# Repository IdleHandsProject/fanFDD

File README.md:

# fanFDD
The firmware and CAD for the neural network fan fault detector.

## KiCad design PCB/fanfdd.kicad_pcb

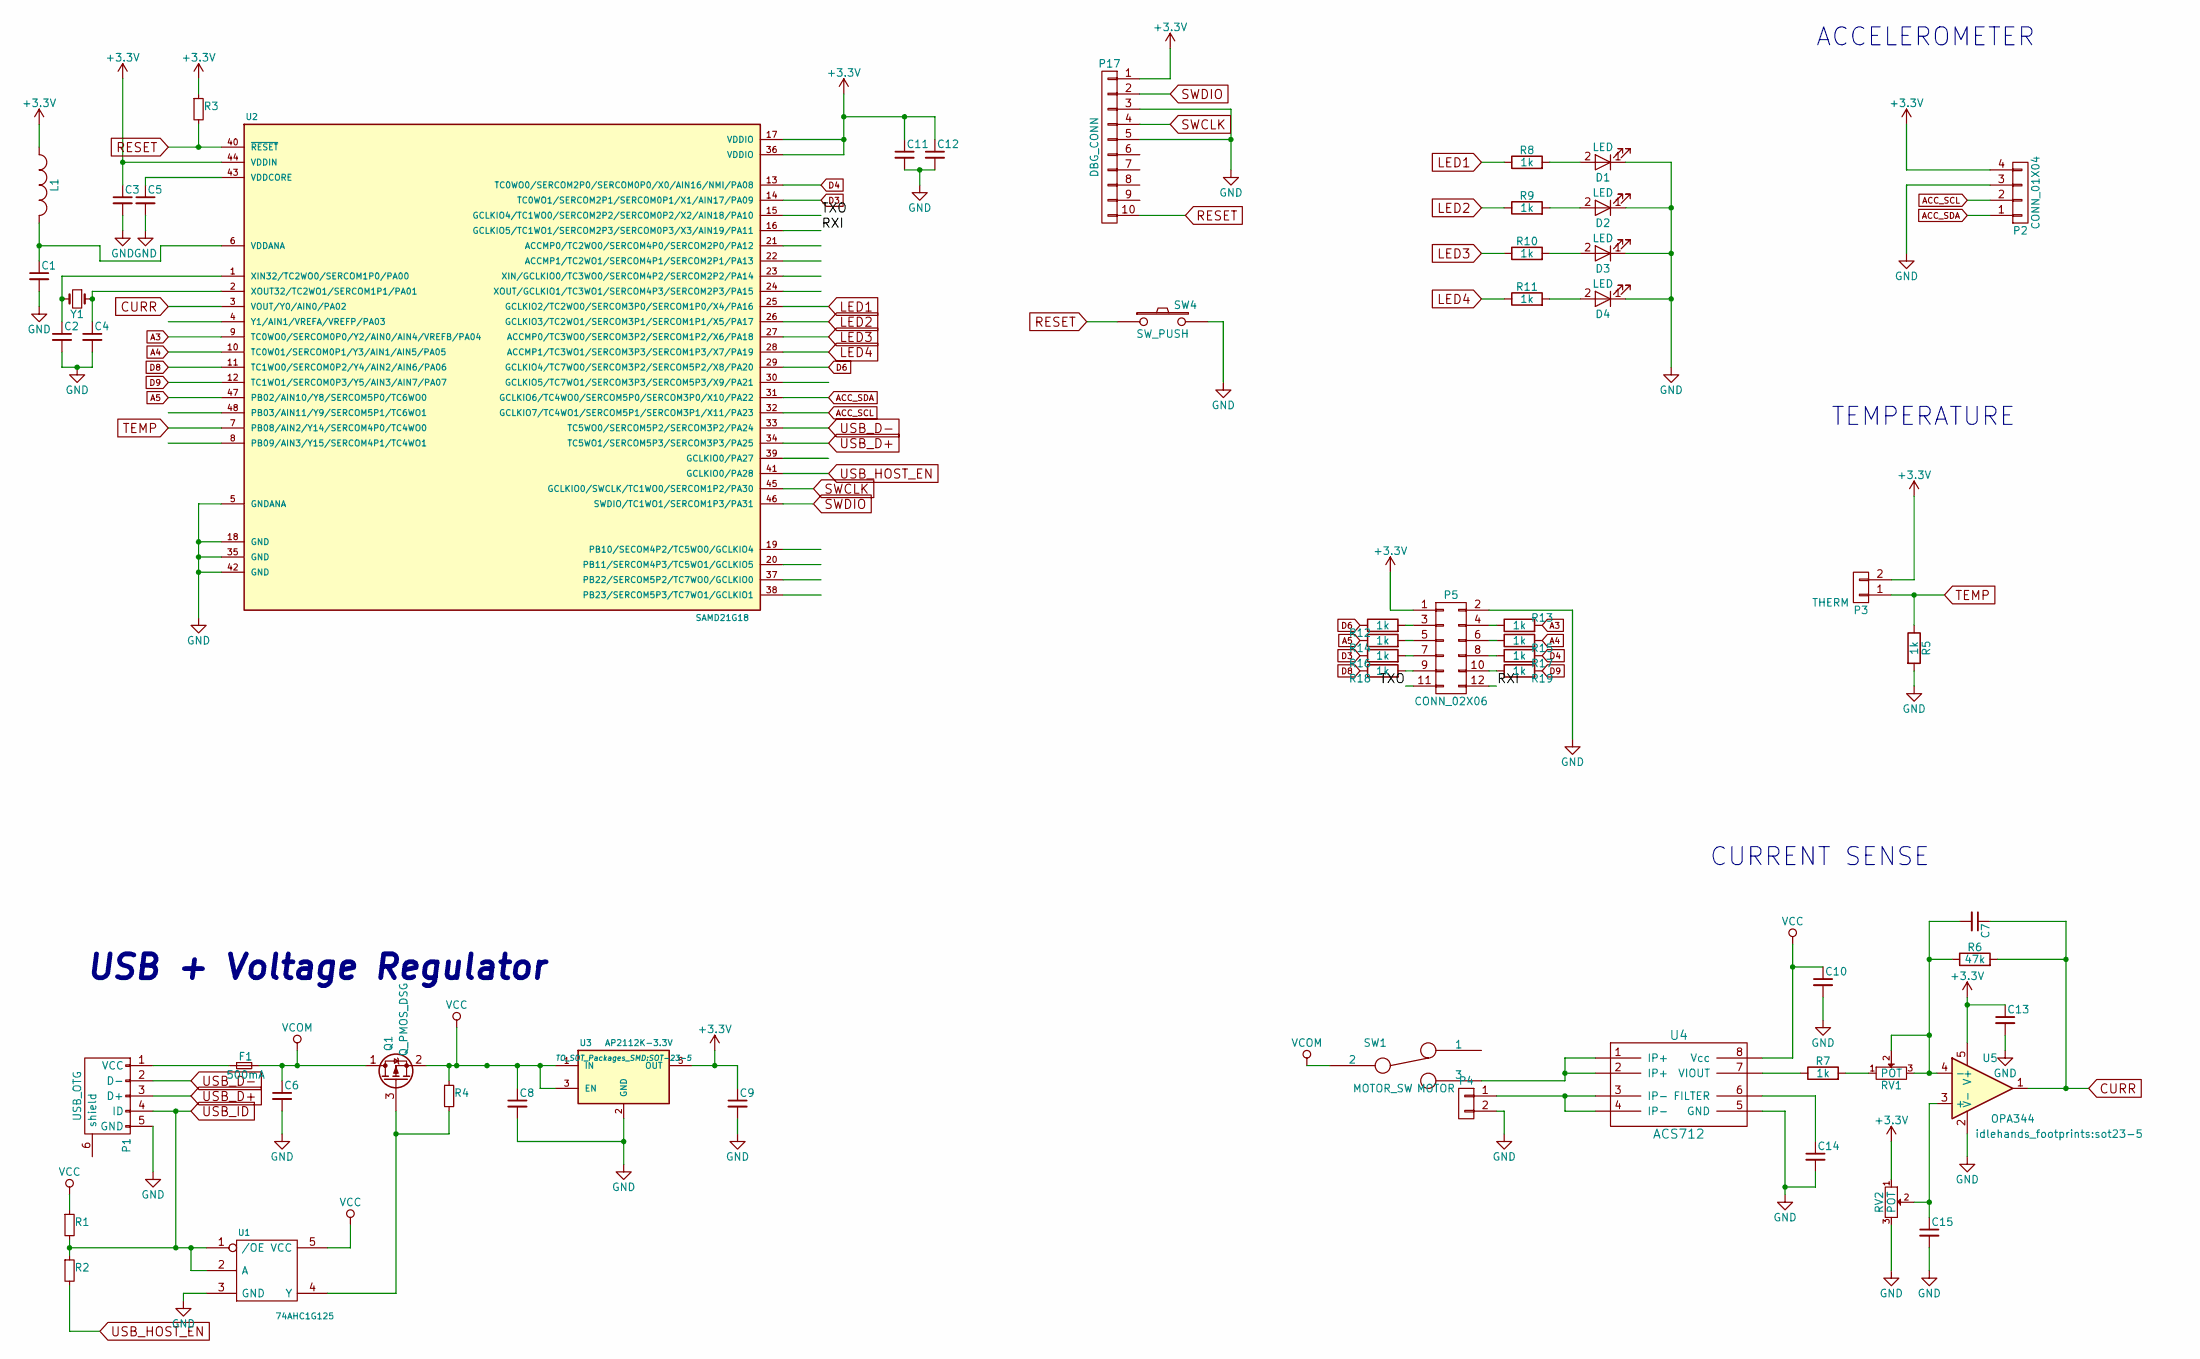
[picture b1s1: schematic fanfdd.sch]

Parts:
C1, C3, C5, C10, C11, C12, C13, C15: 0.1uF; C_0805; Digikey Part No. 1276-1286-1-ND
C2, C4: 15pF; C_0402_Hand; Digikey Part No. 712-1261-1-ND
C6, C9: 2.2uF; C_0805; Digikey Part No. 311-3446-1-ND
C7: 100pF; C_0805; Digikey Part No. 1276-1286-1-ND
C8: 1uF; C_0805; Digikey Part No. 587-1291-1-ND
C14: 1000pF; C_0805; Digikey Part No. 399-1147-1-ND
D1, D2, D3, D4: LED; LED-0603
F1: 500mA; c_1206; Digikey Part No. 507-1803-1-ND
L1: FB - 30Ohm; R_SM0603; Digikey Part No. 445-2986-1-ND
P1: USB_OTG; USB_Micro-B; Digikey Part No. 609-4618-1-ND
P2: CONN_01X04; Pin_Header_Angled_1x04; Digikey Part No. S1111EC-04-ND
P3: THERM; TerminalBlock_Pheonix_PT-3.5mm_2pol; Digikey Part No. 609-4725-ND
P4: MOTOR; TerminalBlock_Pheonix_PT-3.5mm_2pol; Digikey Part No. 609-4725-ND
P5: CONN_02X06; Pin_Header_Straight_2x06_Pitch2.54mm
P17: DBG_CONN; Pin_Header_Straight_2x05_Pitch1.27mm; Digikey Part No. 1175-1627-ND
Q1: Q_PMOS_DSG; SOT23; Digikey Part No. DMG2307L-7DICT-ND
R1: 100k; R_0805; Digikey Part No. 311-100KARCT-ND
R2: 330; R_0805; Digikey Part No. 311-330ARCT-ND
R3: 10k; R_0805; Digikey Part No. 311-10KARCT-ND
R4: 47K; R_0805; Digikey Part No. 311-47KARCT-ND
R5, R7, R8, R9, R10, R11, R12, R13, R14, R15, R16, R17, R18, R19: 1k; R_0805; Digikey Part No. 311-1.0KARCT-ND
R6: 47k; R_0805; Digikey Part No. 311-47KARCT-ND
RV1, RV2: POT; Potentiometer_Bourns_3296W_3-8Zoll_Inline_ScrewUp; Digikey Part No. 490-2875-ND
SW1: MOTOR_SW; OS102011MS2QN1 Slide Switch; Digikey Part No. CKN9565-ND
SW4: SW_PUSH; PTS-LFS; Digikey Part No. CKN9112CT-ND
U1: 74AHC1G125; sot23-5; Digikey Part No. 1727-6024-1-ND
U2: SAMD21G18; TQFP-48_7x7mm_Pitch0.5mm; Digikey Part No. ATSAMD21G18A-AUTCT-ND
U3: AP2112K-3.3V; SOT-23-5; Digikey Part No. AP2112K-3.3TRG1DICT-ND
U4: ACS712; SOIC-8-N; Digikey Part No. 620-1641-1-ND
U5: OPA344; sot23-5; Digikey Part No. OPA344NACT-ND
Y1: Crystal_Small; crystal_smd_3.20x1.50mm2; Digikey Part No. XC1617CT-ND

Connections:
+3V3: C3.1, C9.1, C11.1, C12.1, C13.1, L1.1, P2.4, P3.2, P5.1, P17.1, R3.1, RV2.1, U2.17 (VDDIO), U2.36 (VDDIO), U2.44 (VDDIN), U3.5 (OUT), U5.5 (V+)
/RXI: P5.12, U2.16 (GCLKIO5/TC1WO1/SERCOM2P3/SERCOM0P3/X3/A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)
/TXO: P5.11, U2.15 (GCLKIO4/TC1WO0/SERCOM2P2/SERCOM0P2/X2/A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)
A3: R13.2, U2.9 (TC0WO0/SERCOM0P0/Y2/AIN0/AIN4/VREFB/PA04)
A4: R15.2, U2.10 (TC0W01/SERCOM0P1/Y3/AIN1/AIN5/PA05)
A5: R14.1, U2.47 (PB02/AIN10/Y8/SERCOM5P0/TC6WO0)
ACC_SCL: P2.2, U2.32 (GCLKIO7/TC4WO1/SERCOM5P1/SERCOM3P1/X11/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)
ACC_SDA: P2.1, U2.31 (GCLKIO6/TC4WO0/SERCOM5P0/SERCOM3P0/X10/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)
CURR: C7.1, R6.2, U2.3 (VOUT/Y0/AIN0/PA02), U5.1
D3: R16.1, U2.14 (TC0WO1/SERCOM2P1/SERCOM0P1/X1/AIN17/PA09)
D4: R17.2, U2.13 (TC0WO0/SERCOM2P0/SERCOM0P0/X0/AIN16/NMI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)
D6: R12.1, U2.29 (GCLKIO4/TC7WO0/SERCOM3P2/SERCOM5P2/X8/P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)
D8: R18.1, U2.11 (TC1WO0/SERCOM0P2/Y4/AIN2/AIN6/PA06)
D9: R19.2, U2.12 (TC1WO1/SERCOM0P3/Y5/AIN3/AIN7/PA07)
GND: C1.2, C2.2, C3.2, C4.2, C5.2, C6.2, C8.2, C9.2, C10.2, C11.2, C12.2, C13.2, C14.2, C15.2, D1.1 (K), D2.1 (K), D3.1 (K), D4.1 (K), P1.5 (GND), P2.3, P4.2, P5.2, P17.3, P17.5, R5.2, RV2.3, SW4.2, U1.3 (GND), U2.5 (GNDANA), U2.18 (GND), U2.35 (GND), U2.42 (GND), U3.2 (GND), U4.5 (GND), U5.2 (V-)
LED1: R8.1, U2.25 (GCLKIO2/TC2WO0/SERCOM3P0/SERCOM1P0/X4/P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)
LED2: R9.1, U2.26 (GCLKIO3/TC2WO1/SERCOM3P1/SERCOM1P1/X5/P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)
LED3: R10.1, U2.27 (ACCMP0/TC3WO0/SERCOM3P2/SERCOM1P2/X6/PA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)
LED4: R11.1, U2.28 (ACCMP1/TC3WO1/SERCOM3P3/SERCOM1P3/X7/PA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)
unnamed: C1.1, L1.2, U2.6 (VDDANA)
unnamed: C2.1, U2.1 (XIN32/TC2WO0/SERCOM1P0/PA00), Y1.2
unnamed: C4.1, U2.2 (XOUT32/TC2WO1/SERCOM1P1/PA01), Y1.1
unnamed: C5.1, U2.43 (VDDCORE)
unnamed: C7.2, R6.1, RV1.2, RV1.3, U5.4 (-)
unnamed: C14.1, U4.6 (FILTER)
unnamed: C15.1, RV2.2, U5.3 (+)
unnamed: D1.2 (A), R8.2
unnamed: D2.2 (A), R9.2
unnamed: D3.2 (A), R10.2
unnamed: D4.2 (A), R11.2
unnamed: F1.1, P1.1 (VCC)
unnamed: P4.1, U4.3 (IP-), U4.4 (IP-)
unnamed: P5.3, R12.2
unnamed: P5.4, R13.1
unnamed: P5.5, R14.2
unnamed: P5.6, R15.1
unnamed: P5.7, R16.2
unnamed: P5.8, R17.1
unnamed: P5.9, R18.2
unnamed: P5.10, R19.1
unnamed: Q1.3 (G), R4.2, U1.4 (Y)
unnamed: R7.1, U4.7 (VIOUT)
unnamed: R7.2, RV1.1
unnamed: SW1.3, U4.1 (IP+), U4.2 (IP+)
RESET: P17.10, R3.2, SW4.1, U2.40 (~RESET~)
SWCLK: P17.4, U2.45 (GCLKIO0/SWCLK/TC1WO0/SERCOM1P2/PA30)
SWDIO: P17.2, U2.46 (SWDIO/TC1WO1/SERCOM1P3/PA31)
TEMP: P3.1, R5.1, U2.7 (PB08/AIN2/Y14/SERCOM4P0/TC4WO0)
USB_D+: P1.3 (D+), U2.34 (TC5WO1/SERCOM5P3/SERCOM3P3/PA25)
USB_D-: P1.2 (D-), U2.33 (TC5WO0/SERCOM5P2/SERCOM3P2/PA24)
USB_HOST_EN: R2.2, U2.41 (GCLKIO0/PA28)
USB_ID: P1.4 (ID), R1.2, R2.1, U1.1 (/OE), U1.2 (A)
VCC: C8.1, C10.1, Q1.2 (S), R1.1, R4.1, U1.5 (VCC), U3.1 (IN), U3.3 (EN), U4.8 (Vcc)
VCOM: C6.1, F1.2, Q1.1 (D), SW1.2

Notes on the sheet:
USB + Voltage Regulator
TEMPERATURE
ACCELEROMETER
CURRENT SENSE

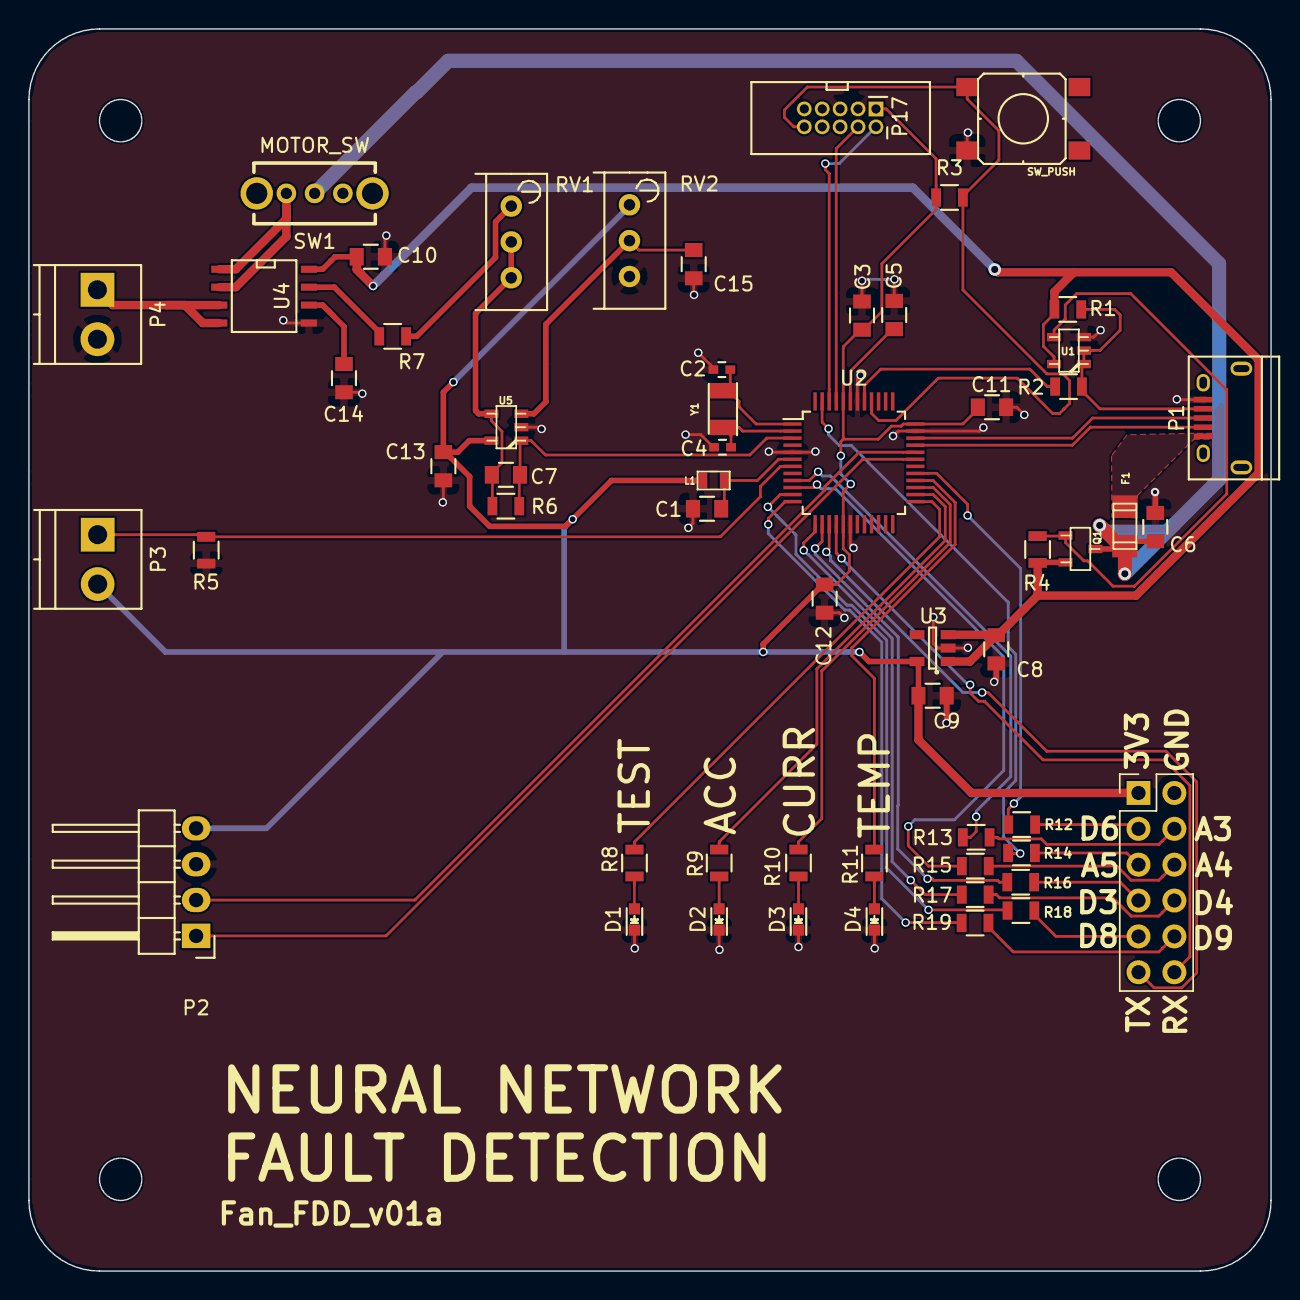
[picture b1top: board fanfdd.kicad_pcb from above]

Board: 2 copper layers, 88.0 x 88.0 mm, 57 parts (0 on the bottom side), 54 nets.

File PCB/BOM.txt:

ref,value,footprint,Digikey Part No.,Mouser Part No.,Quantity
R7 R5 R8 R9 R10 R11 R12 R14 R16 R18 R13 R15 R17 R19,1k,Resistors_SMD:R_0805,311-1.0KARCT-ND,,14
U3,AP2112K-3.3V,TO_SOT_Packages_SMD:SOT-23-5,AP2112K-3.3TRG1DICT-ND,,1
C8,1uF,Capacitors_SMD:C_0805,587-1291-1-ND,,1
P4 P3,MOTOR,Terminal_Blocks:TerminalBlock_Pheonix_PT-3.5mm_2pol,609-4725-ND,,2
Y1,Crystal_Small,idlehands_footprints:crystal_smd_3.20x1.50mm2,XC1617CT-ND,,1
C3 C5 C1 C11 C12 C10 C7 C13 C15,0.1uF,Capacitors_SMD:C_0805,1276-1286-1-ND,,9
F1,500mA,project_footprints:c_1206,507-1803-1-ND,,1
U5,OPA344,idlehands_footprints:sot23-5,OPA344NACT-ND,,1
SW4,SW_PUSH,idlehands_footprints:PTS-LFS,CKN9112CT-ND,,1
C2 C4,15pF,project_footprints:C_0402_Hand,712-1261-1-ND,,2
SW1,MOTOR_SW,idlehands_footprints:OS102011MS2QN1 Slide Switch,CKN9565-ND,,1
P2,CONN_01X04,Pin_Headers:Pin_Header_Angled_1x04,S1111EC-04-ND,,1
U1,74AHC1G125,project_footprints:sot23-5,1727-6024-1-ND,,1
P1,USB_OTG,Connect:USB_Micro-B,609-4618-1-ND,,1
R3,10k,Resistors_SMD:R_0805,311-10KARCT-ND,,1
U2,SAMD21G18,project_footprints:TQFP-48_7x7mm_Pitch0.5mm,ATSAMD21G18A-AUTCT-ND,,1
R4 R6,47K,Resistors_SMD:R_0805,311-47KARCT-ND,,2
P17,DBG_CONN,Pin_Headers:Pin_Header_Straight_2x05_Pitch1.27mm,1175-1627-ND,,1
C14,1000pF,Capacitors_SMD:C_0805,399-1147-1-ND,,1
R1,100k,Resistors_SMD:R_0805,311-100KARCT-ND,,1
Q1,Q_PMOS_DSG,project_footprints:SOT23,DMG2307L-7DICT-ND,,1
R2,330,Resistors_SMD:R_0805,311-330ARCT-ND,,1
C6 C9,2.2uF,Capacitors_SMD:C_0805,311-3446-1-ND,,2
L1,FB - 30Ohm,project_footprints:R_SM0603,445-2986-1-ND,,1
RV1 RV2,POT,Potentiometers:Potentiometer_Bourns_3296W_3-8Zoll_Inline_ScrewUp,490-2875-ND,,2
U4,ACS712,SMD_Packages:SOIC-8-N,620-1641-1-ND,,1

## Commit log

2017-11-24 initial push
2017-11-28 small changes
2020-05-26 updated all files and directories
2020-05-26 added readme
